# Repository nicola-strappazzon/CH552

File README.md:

# CH552G examples

C examples, hardware designs, and notes for the WCH CH552G, an 8-bit microcontroller based on the 8051 architecture. It has native USB and a built-in bootloader, so firmware can be uploaded without a separate programmer.

See the [datasheet](/doc/datasheets/CH552.pdf) and [WCH examples](https://www.wch.cn/downloads/CH552EVT_ZIP.html).

## Specifications

- 3.3 V or 5 V operation.
- 16 KB code flash, 1 KB XRAM, 256 bytes internal RAM, and 128 bytes data flash.
- USB, UART, and SPI.
- Three timers, two PWM channels, and four ADC inputs.
- Built-in bootloader and 24 MHz internal oscillator.
- Factory chip identifier.

The pinout groups functions by colour and marks default and alternate pin mappings. See the [LaTeX sources and build instructions](/doc/pinout) to edit or regenerate it. See the datasheet for all pin functions and package options. Check the clock timing for applications that need accurate delays.

Code flash is rated for about 200 programming cycles at 5 V. Data flash is rated for about 10,000 erase/write cycles; spread writes across it to reduce wear.

## Minimum circuit

- One CH552G.
- Two 100 nF capacitors.
- Two 10 kΩ resistors.
- Two 1 kΩ resistors.
- Two buttons: boot and reset.

## Examples

- [ADC](/src/adc): read a potentiometer and send values over UART.
- [Blink](/src/blink): blink an LED.
- [Bootloader](/src/bootloader): enter the bootloader at startup.
- [Button](/src/button): control an LED with a button.
- [Button and RGB LED](/src/button_led_rgb): change color with a button.
- [UART](/src/cdc): send and receive text through a CH340 adapter.
- [Data flash](/src/data_flash): save the last LED color.
- [DHT11](/src/dht11): show temperature and humidity on an OLED.
- [DHT20](/src/dht20): wiring notes; sensor code is not implemented yet.
- [DS1307](/src/ds1307): show the date and time on an OLED.
- [Fade](/src/fade): fade an LED with software PWM.
- [Hardware PWM](/src/pwm): fade an LED with PWM1.
- [SSD1306](/src/ssd1306): write text to an I2C OLED.
- [Unique ID](/src/unique_id): send chip configuration bytes over USB CDC.
- [USB CDC TX](/src/usb/cdc/tx): send text over USB.
- [USB CDC RX](/src/usb/cdc/rx): echo bytes received over USB.
- [Watchdog](/src/watchdog): reset after a simulated hang.

## Documentation

- [Pinout](/doc/pinout): LaTeX sources, peripheral groups, pin mappings, and diagram build instructions.
- [SDCC](/doc/sdcc.md): install the compiler and build examples.
- [Bootloader](/doc/bootloader.md): enter upload mode.
- [Flash](/doc/flash.md): upload firmware with wchisp.
- [Hardware](/hdw): KiCad designs.
- [Links](/doc/links.md): related resources.

## Related projects

- [CH334 - USB 2.0 hub](https://github.com/nicola-strappazzon/CH334)
- [CH340 - USB to serial](https://github.com/nicola-strappazzon/CH340)
- [CH9141 - Bluetooth serial](https://github.com/nicola-strappazzon/CH9141)

## Third-party projects

- [Adafruit CH552 QT Py](https://learn.adafruit.com/adafruit-ch552-qt-py/overview)
- [CH559 documentation in English](https://kprasadvnsi.github.io/CH559_Doc_English)
- [ch55xduino](https://github.com/DeqingSun/ch55xduino)
- [CH552 debugger for Arduino Uno](https://github.com/DeqingSun/unoDebugTestPackage)

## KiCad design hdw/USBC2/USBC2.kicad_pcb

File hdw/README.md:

# Hardware

[KiCad](https://www.kicad.org) designs for CH552G projects. The boards can be manufactured by services such as [JLCPCB](https://jlcpcb.com).

## Minimum circuit

[KiCad files](minimal) for the minimum CH552G circuit.

## SOIC-16 breakout

Breakout board for breadboard use. Only the image is included here.

## TQFP-48 breakout

[KiCad files](TQFP48) for a TQFP-48 breadboard adapter.

## USB-C breakout

[KiCad files](USBC2) for a USB-C connector adapter with mechanical support.

## CH552G board

[KiCad files](CH552G) for a board with the CH552G circuit.

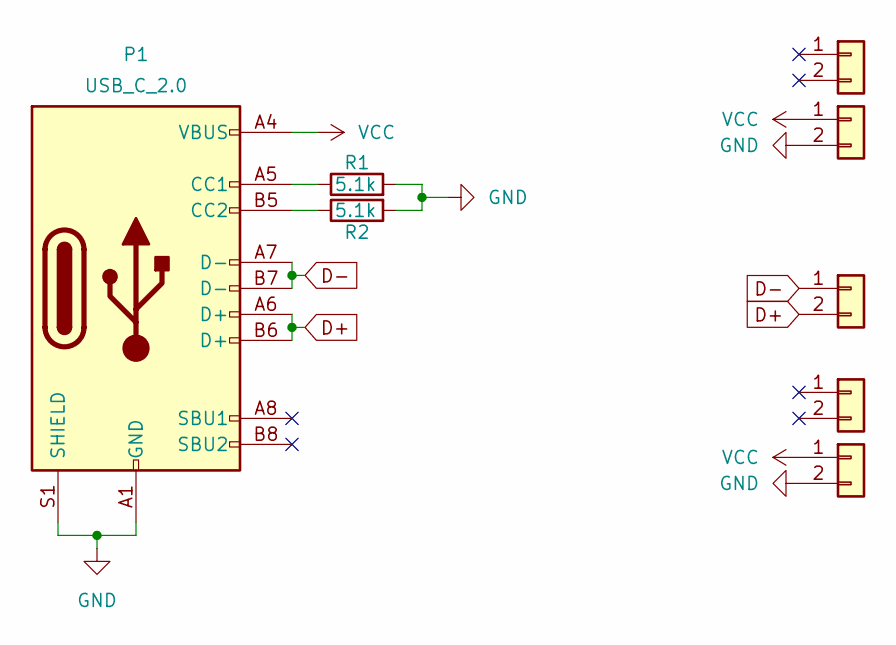
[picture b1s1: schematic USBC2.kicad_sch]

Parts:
J1, J2, J3, J4, J6: Conn_01x02; PinHeader_1x02_P2.54mm_Vertical
P1: USB_C_2.0; USB_C_Receptacle_GCT_USB4085
R1, R2: 5.1k; R_1206_3216Metric_Pad1.30x1.75mm_HandSolder

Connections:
D+: J3.2, P1.A6 (D+), P1.B6 (D+)
D-: J3.1, P1.A7 (D-), P1.B7 (D-)
GND: J1.2, J6.2, P1.A1 (GND), P1.A12 (GND), P1.B1 (GND), P1.B12 (GND), P1.S1 (SHIELD), R1.2, R2.2
unnamed: P1.A5 (CC1), R1.1
unnamed: P1.B5 (CC2), R2.1
VCC: J1.1, J6.1, P1.A4 (VBUS), P1.A9 (VBUS), P1.B4 (VBUS), P1.B9 (VBUS)

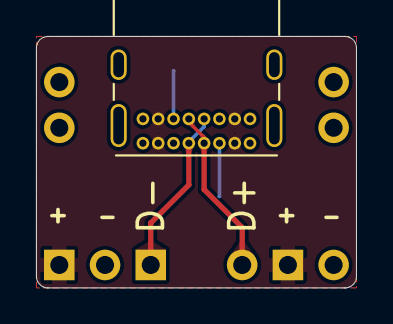
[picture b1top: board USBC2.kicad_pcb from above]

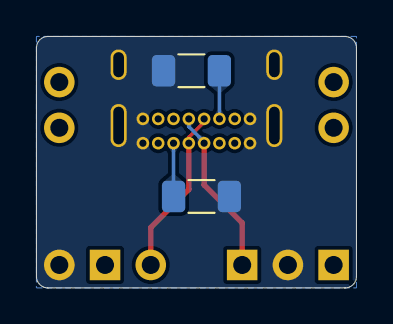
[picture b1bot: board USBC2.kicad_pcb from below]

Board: 2 copper layers, 17.8 x 14.0 mm, 8 parts (7 on the bottom side), 6 nets.

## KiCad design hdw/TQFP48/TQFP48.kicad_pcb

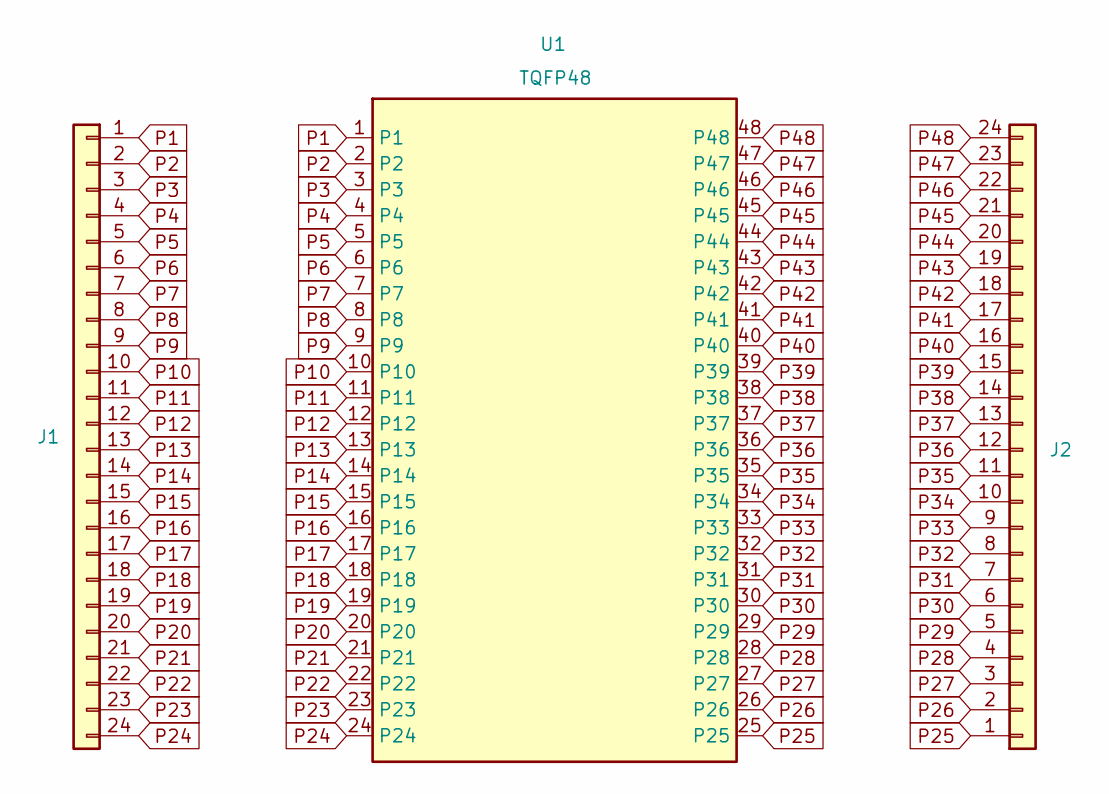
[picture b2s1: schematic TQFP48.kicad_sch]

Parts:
J1, J2: Conn_01x24; PinHeader_1x24_P2.54mm_Vertical
U1: TQFP48; TQFP-48_7x7mm_P0.5mm

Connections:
P1: J1.1, U1.1
P2: J1.2, U1.2
P3: J1.3, U1.3
P4: J1.4, U1.4
P5: J1.5, U1.5
P6: J1.6, U1.6
P7: J1.7, U1.7
P8: J1.8, U1.8
P9: J1.9, U1.9
P10: J1.10, U1.10
P11: J1.11, U1.11
P12: J1.12, U1.12
P13: J1.13, U1.13
P14: J1.14, U1.14
P15: J1.15, U1.15
P16: J1.16, U1.16
P17: J1.17, U1.17
P18: J1.18, U1.18
P19: J1.19, U1.19
P20: J1.20, U1.20
P21: J1.21, U1.21
P22: J1.22, U1.22
P23: J1.23, U1.23
P24: J1.24, U1.24
P25: J2.1, U1.25
P26: J2.2, U1.26
P27: J2.3, U1.27
P28: J2.4, U1.28
P29: J2.5, U1.29
P30: J2.6, U1.30
P31: J2.7, U1.31
P32: J2.8, U1.32
P33: J2.9, U1.33
P34: J2.10, U1.34
P35: J2.11, U1.35
P36: J2.12, U1.36
P37: J2.13, U1.37
P38: J2.14, U1.38
P39: J2.15, U1.39
P40: J2.16, U1.40
P41: J2.17, U1.41
P42: J2.18, U1.42
P43: J2.19, U1.43
P44: J2.20, U1.44
P45: J2.21, U1.45
P46: J2.22, U1.46
P47: J2.23, U1.47
P48: J2.24, U1.48

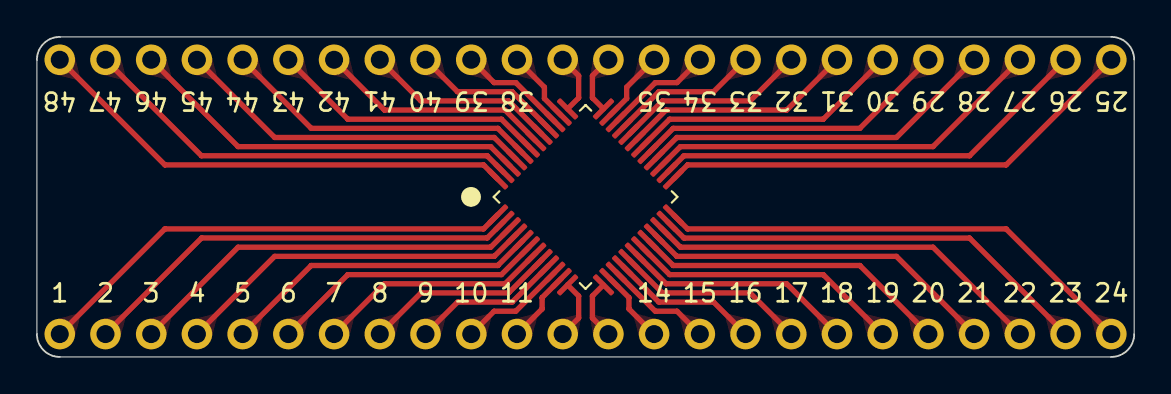
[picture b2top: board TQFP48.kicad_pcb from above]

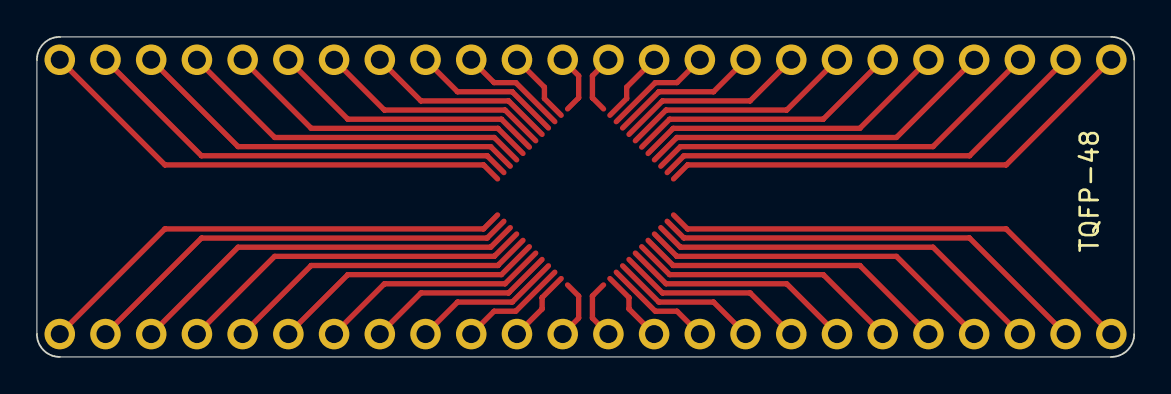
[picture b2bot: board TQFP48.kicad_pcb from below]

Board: 2 copper layers, 61.0 x 17.8 mm, 3 parts (2 on the bottom side), 48 nets.

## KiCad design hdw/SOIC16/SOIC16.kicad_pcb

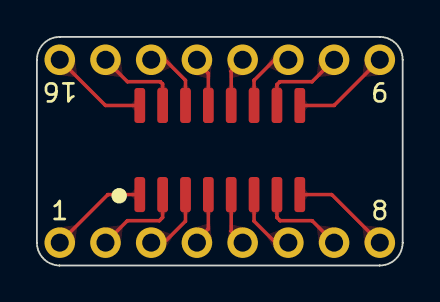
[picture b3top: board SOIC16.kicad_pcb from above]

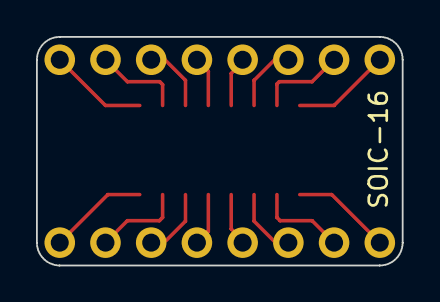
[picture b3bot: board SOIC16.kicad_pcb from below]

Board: 2 copper layers, 20.3 x 12.7 mm, 3 parts (2 on the bottom side), 16 nets.

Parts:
J16: SOIC16-P01-P08; PinHeader_1x08_P2.54mm_Vertical
J17: SOIC16-P09-P16; PinHeader_1x08_P2.54mm_Vertical
U5: CH340C; SOIC-16_3.9x9.9mm_P1.27mm

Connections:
SOIC16-P01: J16.1, U5.1 (GND)
SOIC16-P02: J16.2, U5.2 (TXD)
SOIC16-P03: J16.3, U5.3 (RXD)
SOIC16-P04: J16.4, U5.4 (V3)
SOIC16-P05: J16.5, U5.5 (UD+)
SOIC16-P06: J16.6, U5.6 (UD-)
SOIC16-P07: J16.7, U5.7 (NC)
SOIC16-P08: J16.8, U5.8 (NC)
SOIC16-P09: J17.1, U5.9 (~CTS)
SOIC16-P10: J17.2, U5.10 (~DSR)
SOIC16-P11: J17.3, U5.11 (~RI)
SOIC16-P12: J17.4, U5.12 (~DCD)
SOIC16-P13: J17.5, U5.13 (~DTR)
SOIC16-P14: J17.6, U5.14 (~RTS)
SOIC16-P15: J17.7, U5.15 (R232)
SOIC16-P16: J17.8, U5.16 (VCC)

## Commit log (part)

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2025-04-15 Save changes at: 1744735870
2025-05-25 Save changes at: 1748167978
2025-05-25 Save changes at: 1748169979
2025-05-25 Save changes at: 1748170080
2025-05-25 Save changes at: 1748186389
2025-05-25 Save changes at: 1748195240
2025-05-25 Save changes at: 1748198005
2025-05-26 Save changes at: 1748303287
2025-05-27 Save changes at: 1748380927
2025-05-27 Save changes at: 1748381225
2025-05-27 Save changes at: 1748381372
2025-05-27 Save changes at: 1748381587
2025-05-27 Save changes at: 1748381827
2025-05-28 Save changes at: 1748460130
2025-05-28 Save changes at: 1748460734
2025-05-30 Save changes at: 1748616972
2025-05-30 Save changes at: 1748649397
2025-05-31 Save changes at: 1748680191
2025-05-31 Save changes at: 1748707241
2025-06-30 Save changes at: 1751310596
2025-11-02 Fix links for CH552 datasheet
2025-11-02 Make references local allowing offline usage
2025-11-18 Save changes at: 1763455265
2026-05-10 Save changes at: 1778399588
2026-05-11 Add example about unique id and few changes in usb/cdc/tx
2026-05-12 add pwm by hardware without ISR
2026-05-16 feat: usb tx & rx
2026-05-16 Save changes at: 1778920571
2026-05-16 Save changes at: 1778956092
2026-05-16 Save changes at: 1778956133
2026-05-16 Save changes at: 1778956581
2026-05-16 Save changes at: 1778956636
2026-05-16 Save changes at: 1778956837
2026-05-16 Save changes at: 1778956907
2026-05-16 Save changes at: 1778957242
2026-05-16 Save changes at: 1778957393
